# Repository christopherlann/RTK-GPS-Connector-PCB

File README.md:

# RTK-GPS-Connector-PCB
KiCad files for the connector PCB for the RTK-GPS project

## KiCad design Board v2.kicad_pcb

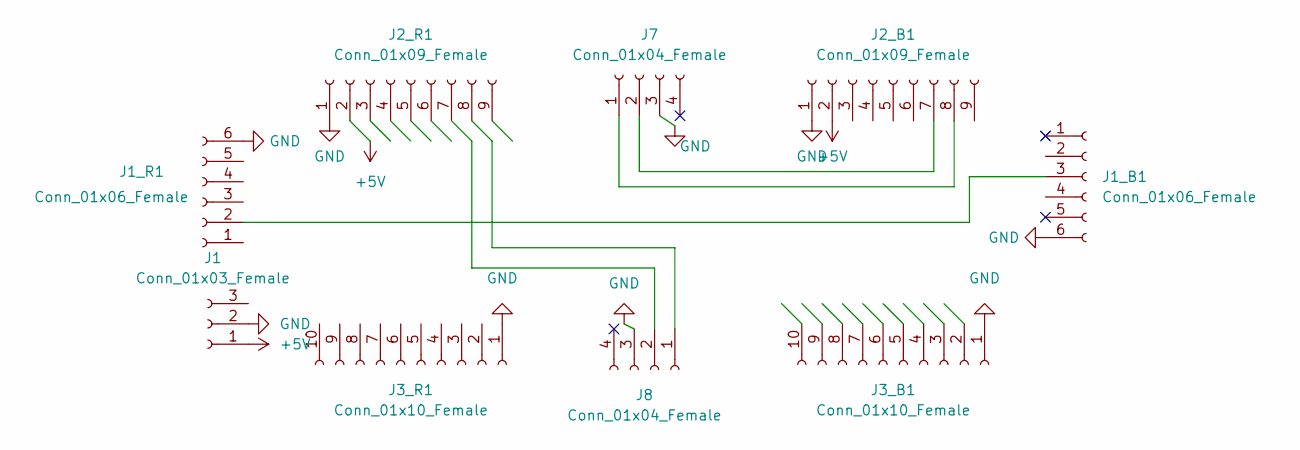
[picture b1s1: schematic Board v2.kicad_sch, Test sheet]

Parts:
J1: Conn_01x03_Female; Molex_Micro-Fit_3.0_43650-0300_1x03_P3.00mm_Horizontal
J1_B1, J1_R1: Conn_01x06_Female; PinSocket_1x06_P2.54mm_Vertical
J2_B1, J2_R1: Conn_01x09_Female; PinSocket_1x09_P2.54mm_Vertical
J3_B1, J3_R1: Conn_01x10_Female; PinSocket_1x10_P2.54mm_Vertical
J7, J8: Conn_01x04_Female; JST_GH_SM04B-GHS-TB_1x04-1MP_P1.25mm_Horizontal

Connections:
+5V: J1.1, J2_B1.2, J2_R1.2
GND: J1.2, J1_B1.6, J1_R1.6, J2_B1.1, J2_R1.1, J3_B1.1, J3_R1.1, J7.3, J8.3
unnamed: J1_B1.3, J1_R1.2
unnamed: J2_B1.7, J7.2
unnamed: J2_B1.8, J7.1
unnamed: J2_R1.7, J8.2
unnamed: J2_R1.8, J8.1

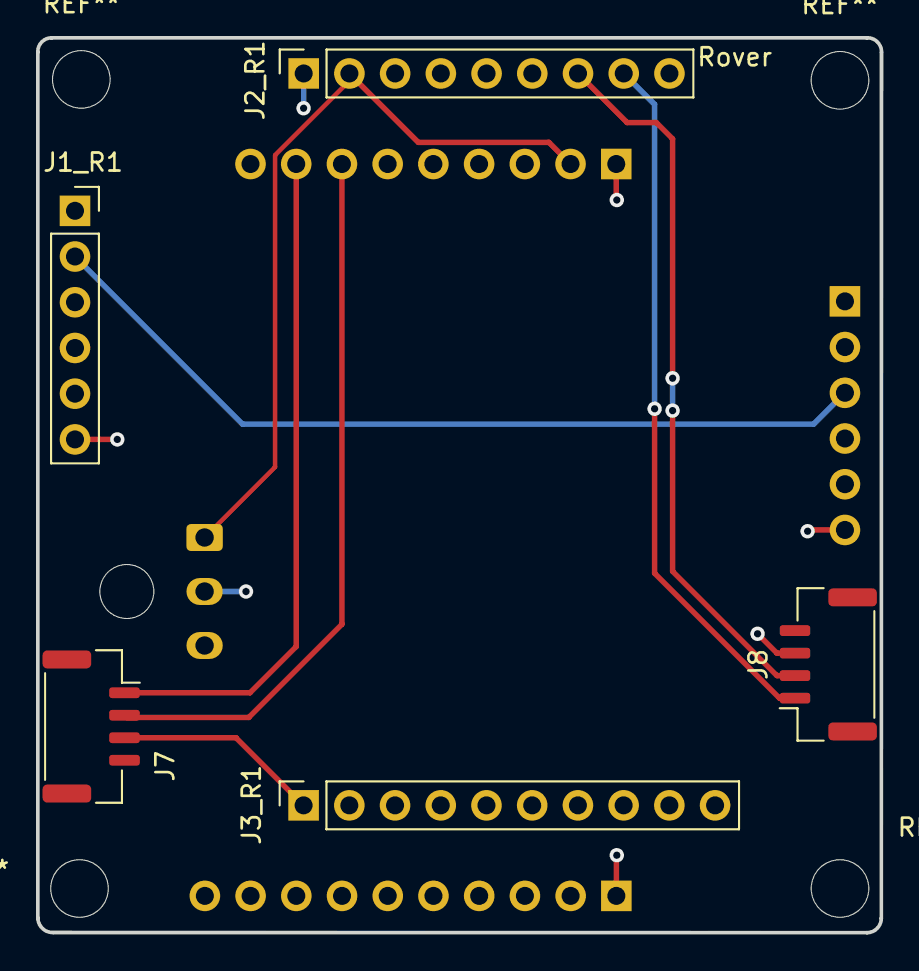
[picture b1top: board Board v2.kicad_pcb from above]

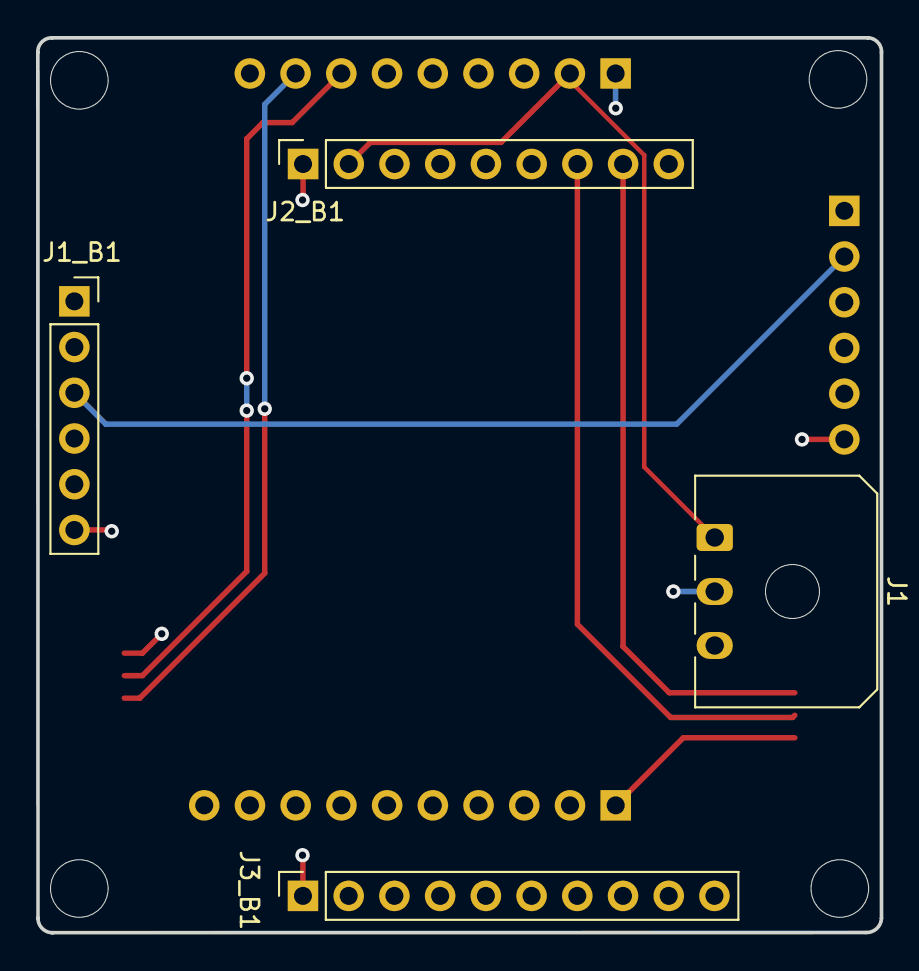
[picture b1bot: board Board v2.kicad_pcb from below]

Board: 4 copper layers, 46.9 x 49.7 mm, 9 parts (4 on the bottom side), 7 nets.
